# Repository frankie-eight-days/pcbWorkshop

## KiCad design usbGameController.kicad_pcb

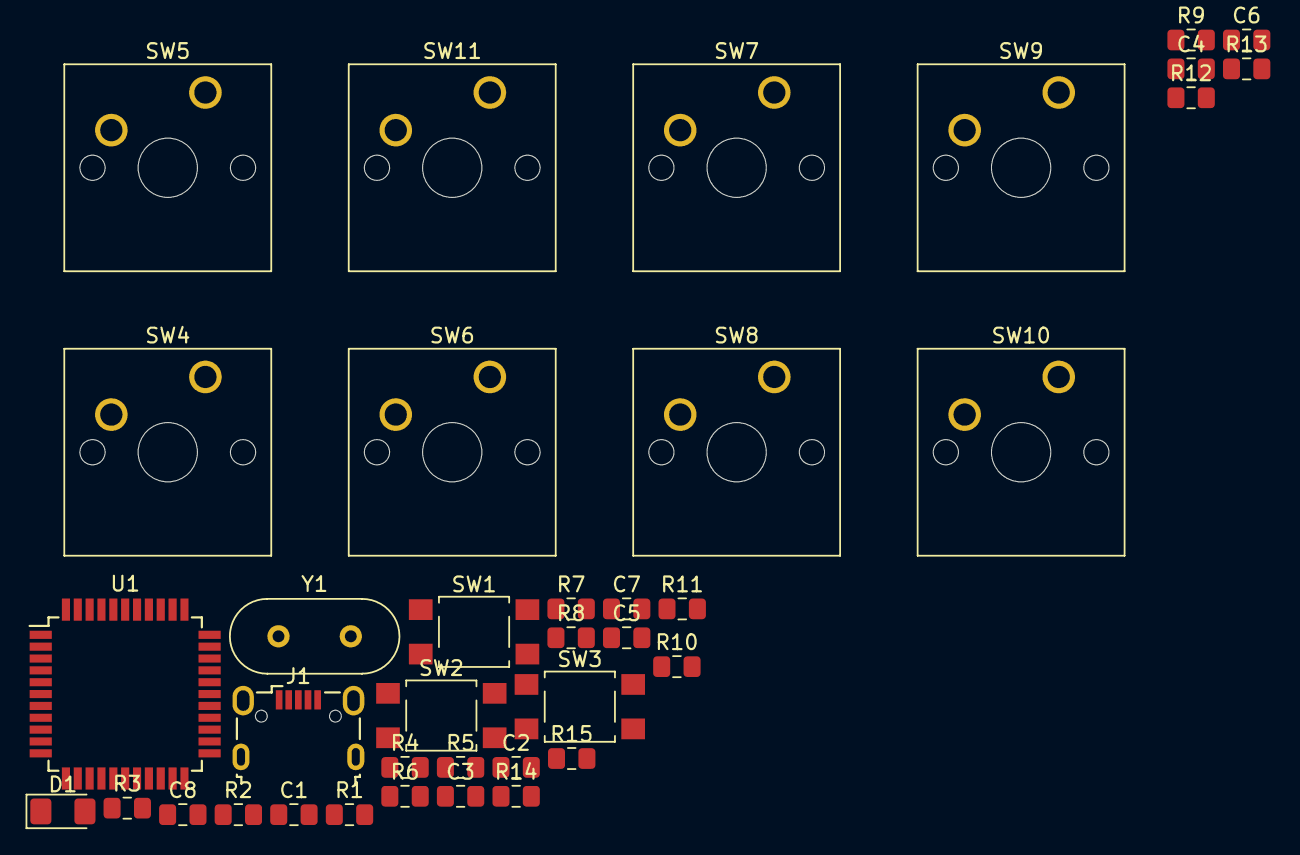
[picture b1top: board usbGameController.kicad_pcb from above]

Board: 2 copper layers, 38 parts (0 on the bottom side), 22 nets, no tracks yet.

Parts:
C1: 1u; C_0805_2012Metric_Pad1.15x1.40mm_HandSolder
C2, C3, C4, C5: .1u; C_0805_2012Metric_Pad1.15x1.40mm_HandSolder
C6: 4.7u; C_0805_2012Metric_Pad1.15x1.40mm_HandSolder
C7, C8: 22p; C_0805_2012Metric_Pad1.15x1.40mm_HandSolder
D1: LED; LED_1206_3216Metric_Pad1.42x1.75mm_HandSolder
J1: USB_B_Micro; USB_Micro-B_Wuerth_629105150521
R1, R2: 22; R_0805_2012Metric_Pad1.15x1.40mm_HandSolder
R3, R4, R5, R6, R7, R8, R9, R10, R11, R12, R13, R14, R15: 10k; R_0805_2012Metric_Pad1.15x1.40mm_HandSolder
SW1, SW2, SW3: SW_Push; SW_SPST_TL3305A
SW4, SW5, SW6, SW7, SW8, SW9, SW10, SW11: SW_SPST; SW_Cherry_MX1A_1.00u_PCB
U1: ATmega32U4-AU; TQFP-44_10x10mm_P0.8mm
Y1: Crystal; Crystal_HC49-4H_Vertical

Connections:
/A: R14.2, SW5.1, U1.19
/A2: R9.2, SW10.1, U1.26
/B: R8.2, SW11.1, U1.27
/D: R12.2, SW7.1, U1.21
/S: R13.2, SW6.1, U1.20
/W: R15.2, SW4.1, U1.18
/X: R11.2, SW8.1, U1.25
/XTAL1: C7.2, U1.17, Y1.1
/XTAL2: C8.2, U1.16, Y1.2
/Y: R10.2, SW9.1, U1.22
/select: R6.2, SW3.1
/start: R7.2, SW2.1
GND: C1.1, C2.2, C3.2, C4.2, C5.2, C6.2, C7.1, C8.1, J1.5, J1.6, R4.2, R5.1, SW1.1, SW2.2, SW3.2, SW4.2, SW5.2, SW6.2, SW7.2, SW8.2, SW9.2, SW10.2, SW11.2, U1.5, U1.15, U1.23, U1.35, U1.43
unnamed: C1.2, U1.6
unnamed: D1.1, R4.1
unnamed: J1.2, R2.2
unnamed: J1.3, R1.2
unnamed: R1.1, U1.4
unnamed: R2.1, U1.3
unnamed: R3.2, SW1.2, U1.13
unnamed: R5.2, U1.33
VCC: C2.1, C3.1, C4.1, C5.1, C6.1, D1.2, J1.1, R3.1, R6.1, R7.1, R8.1, R9.1, R10.1, R11.1, R12.1, R13.1, R14.1, R15.1, U1.2, U1.7, U1.14, U1.24, U1.34, U1.44

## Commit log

2018-11-03 workshop files
